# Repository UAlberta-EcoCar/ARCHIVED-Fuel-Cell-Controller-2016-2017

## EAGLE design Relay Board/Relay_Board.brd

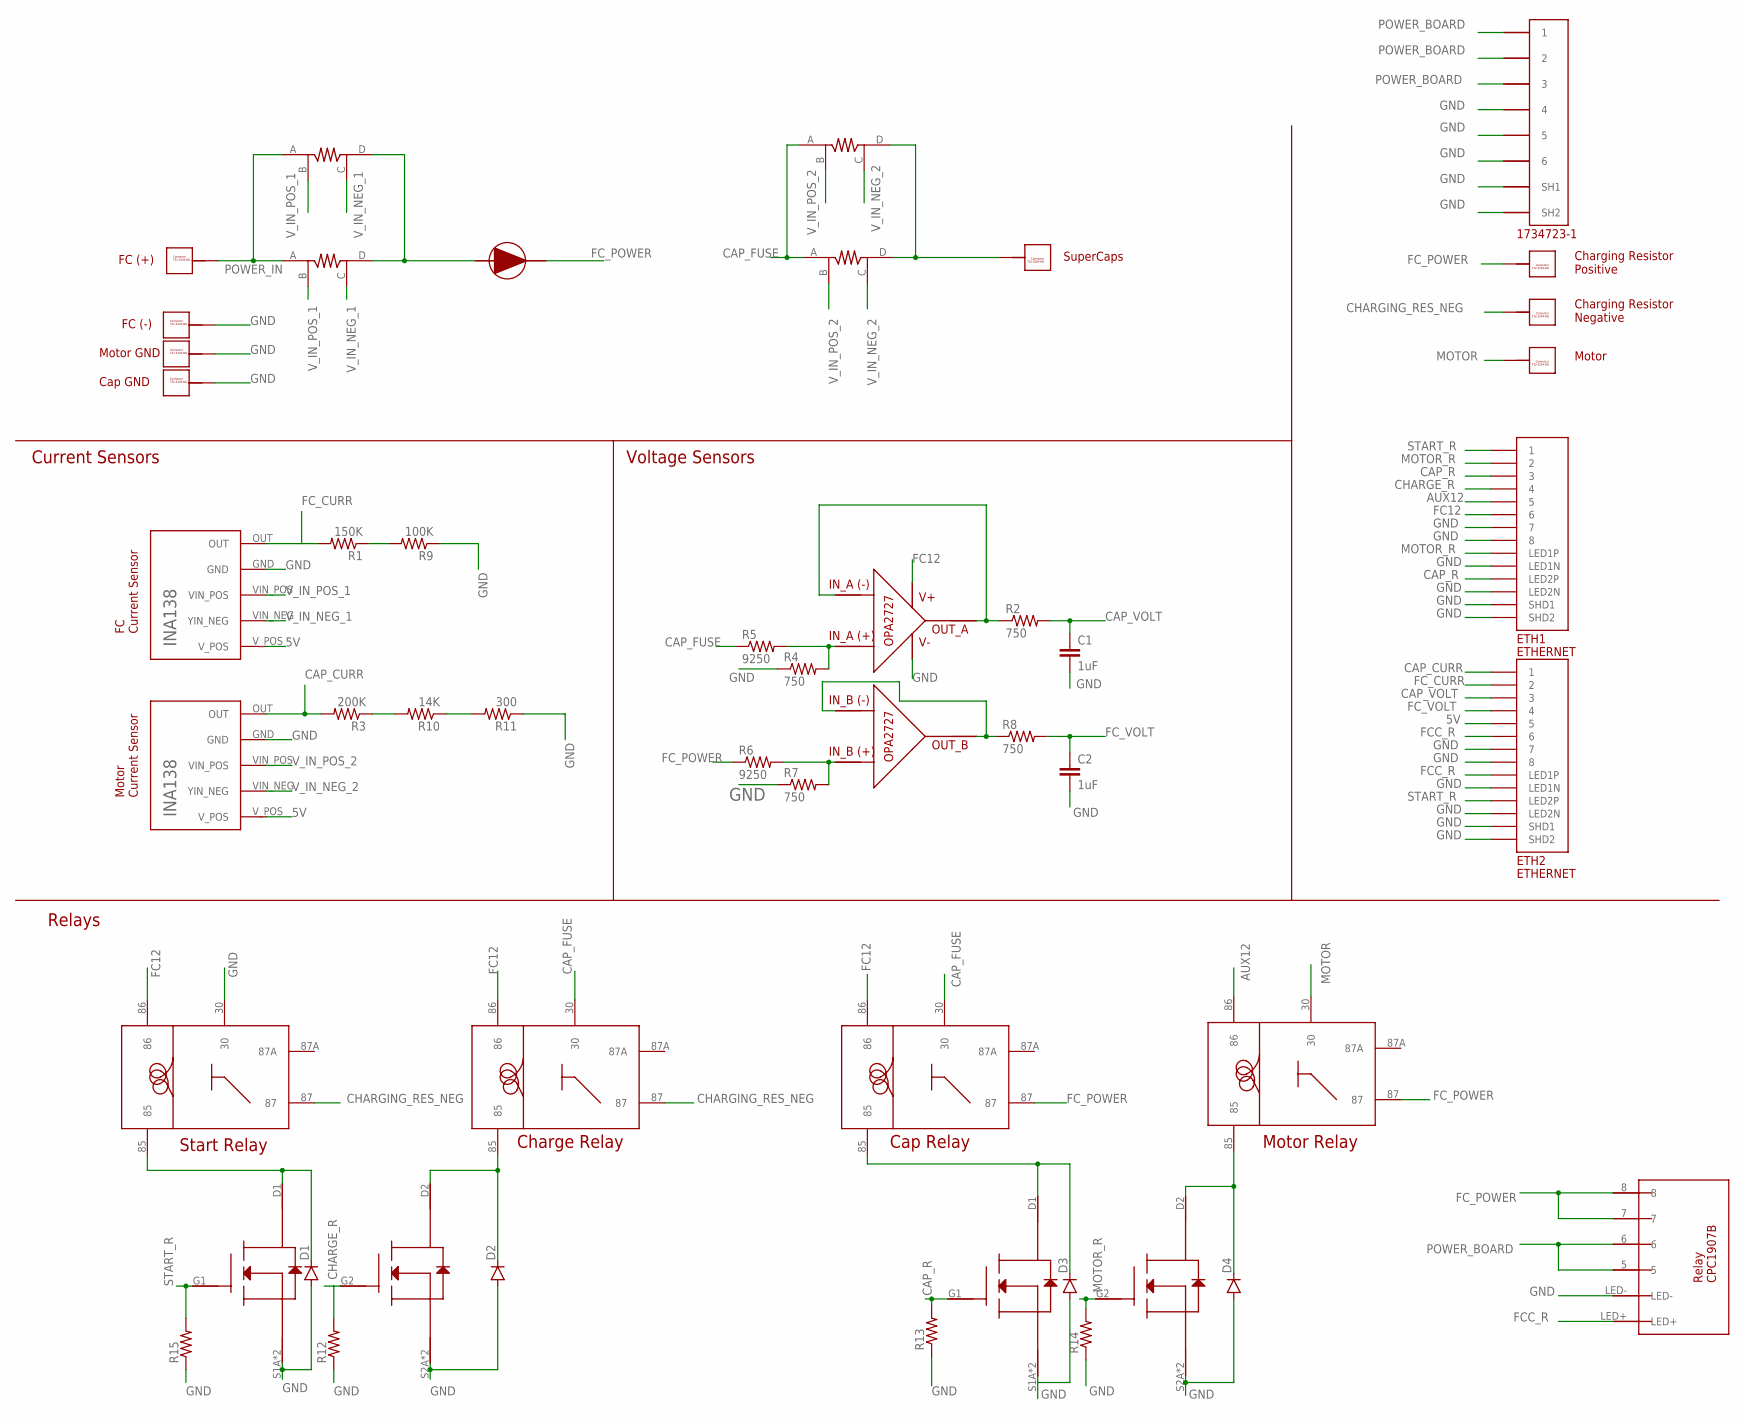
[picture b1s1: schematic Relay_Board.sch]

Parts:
C1, C2: 1uF; 0402-CAP
D1, D2, D3, D4: DIODESOD123; SOD-123
ETH1, ETH2: ETHERNET; A122645-ND
R1: 150K; 1206
R2, R4, R7, R8: 750; 1206
R3: 200K; 1206
R5, R6: 9250; 1206
R9: 100K; 1206
R10: 14K; 1206
R11: 300; 1206
R12, R13, R14, R15: RESISTOR0603-RES; 0603-RES
U$1, U$2, U$10, U$13, U$14, U$20, U$23, U$24: 732-3204-ND_CONNECTOR; 732-3204-ND
U$3, U$7: TI_INA138
U$4, U$6, U$12, U$21: SHUNT_RESISTOR_CSM3637; CSM3637
U$5: DIODE-APT60S20BG
U$8, U$11, U$15, U$18: VCF4-1000
U$9, U$25: SI6926ADQ-T1-E3CT-ND_MOSFET
U$17: OP-AMP_OPA2727AIDR
U$19: 5555140-6; 1734723-1_RJ11
U$22: RELAY-CPC1907B

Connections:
5V: ETH2.P$5 (5), U$3.V_POS, U$7.V_POS
AUX12: ETH1.P$5 (5), U$18.86
CAP_CURR: ETH2.P$1 (1), R3.2, U$3.OUT
CAP_FUSE: R5.1, U$8.30, U$11.30, U$12.A, U$21.A
CAP_R: ETH1.P$3 (3), ETH1.P$12 (LED2P), R13.2, U$9.G1
CAP_VOLT: C1.1, ETH2.P$3 (3), R2.2
CHARGE_R: ETH1.P$4 (4), R12.2, U$25.G2
CHARGING_RES_NEG: U$11.87, U$14.P$1, U$14.P$2, U$14.P$3, U$14.P$4, U$14.P$5, U$14.P$6, U$14.P$7, U$14.P$8, U$14.P$9, U$14.P$10, U$15.87
FC12: ETH1.P$6 (6), U$8.86, U$11.86, U$15.86, U$17.V+
FCC_R: ETH2.P$6 (6), ETH2.P$10 (LED1P), U$22.LED+
FC_CURR: ETH2.P$2 (2), R1.2, U$7.OUT
FC_POWER: R6.1, U$5.CATHODE, U$8.87, U$13.P$1, U$13.P$2, U$13.P$3, U$13.P$4, U$13.P$5, U$13.P$6, U$13.P$7, U$13.P$8, U$13.P$9, U$13.P$10, U$18.87, U$22.7, U$22.8
FC_VOLT: C2.1, ETH2.P$4 (4), R8.2
GND: C1.2, C2.2, D1.A, D2.A, D3.A, D4.A, ETH1.P$7 (7), ETH1.P$8 (8), ETH1.P$9 (LED1N), ETH1.P$11 (LED2N), ETH1.P$13 (SHD1), ETH1.P$14 (SHD2), ETH2.P$7 (7), ETH2.P$8 (8), ETH2.P$9 (LED1N), ETH2.P$11 (LED2N), ETH2.P$13 (SHD1), ETH2.P$14 (SHD2), R4.1, R7.1, R9.1, R11.1, R12.1, R13.1, R14.1, R15.1, U$2.P$1, U$2.P$2, U$2.P$3, U$2.P$4, U$2.P$5, U$2.P$6, U$2.P$7, U$2.P$8, U$2.P$9, U$2.P$10, U$3.GND, U$7.GND, U$9.S1A (S1), U$9.S1B (S1), U$9.S2A (S2), U$9.S2B (S2), U$15.30, U$17.V-, U$19.4, U$19.5, U$19.6, U$19.SH1, U$19.SH2, U$22.LED-, U$23.P$1, U$23.P$2, U$23.P$3, U$23.P$4, U$23.P$5, U$23.P$6, U$23.P$7, U$23.P$8, U$23.P$9, U$23.P$10, U$24.P$1, U$24.P$2, U$24.P$3, U$24.P$4, U$24.P$5, U$24.P$6, U$24.P$7, U$24.P$8, U$24.P$9, U$24.P$10, U$25.S1A (S1), U$25.S1B (S1), U$25.S2A (S2), U$25.S2B (S2)
MOTOR: U$18.30, U$20.P$1, U$20.P$2, U$20.P$3, U$20.P$4, U$20.P$5, U$20.P$6, U$20.P$7, U$20.P$8, U$20.P$9, U$20.P$10
MOTOR_R: ETH1.P$2 (2), ETH1.P$10 (LED1P), R14.2, U$9.G2
unnamed: R1.1, R9.2
unnamed: D3.C, U$8.85, U$9.D1
unnamed: D1.C, U$15.85, U$25.D1
unnamed: D2.C, U$11.85, U$25.D2
unnamed: R4.2, R5.2, U$17.IN_A+
unnamed: R6.2, R7.2, U$17.IN_B+
unnamed: R8.1, U$17.IN_B-, U$17.OUT_B
unnamed: R2.1, U$17.IN_A-, U$17.OUT_A
unnamed: R3.1, R10.2
unnamed: R10.1, R11.2
unnamed: D4.C, U$9.D2, U$18.85
POWER_BOARD: U$19.1, U$19.2, U$19.3, U$22.5, U$22.6
POWER_IN: U$1.P$1, U$1.P$2, U$1.P$3, U$1.P$4, U$1.P$5, U$1.P$6, U$1.P$7, U$1.P$8, U$1.P$9, U$1.P$10, U$4.A, U$6.A
SHUNT_RES_1: U$4.D, U$5.ANODE, U$6.D
START_R: ETH1.P$1 (1), ETH2.P$12 (LED2P), R15.2, U$25.G1
SUPERCAPS: U$10.P$1, U$10.P$2, U$10.P$3, U$10.P$4, U$10.P$5, U$10.P$6, U$10.P$7, U$10.P$8, U$10.P$9, U$10.P$10, U$12.D, U$21.D
V_IN_NEG_1: U$4.C, U$6.C, U$7.VIN_NEG (YIN_NEG)
V_IN_NEG_2: U$3.VIN_NEG (YIN_NEG), U$12.C, U$21.C
V_IN_POS_1: U$4.B, U$6.B, U$7.VIN_POS
V_IN_POS_2: U$3.VIN_POS, U$12.B, U$21.B

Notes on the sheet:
FC Current Sensor
SuperCaps
Charging Resistor Positive
Charging Resistor Negative
Motor Current Sensor
FC (+)
FC (-)
Motor
Voltage Sensors
Current Sensors
Relays
Cap Relay
Charge Relay
Start Relay
Motor Relay
Motor GND
Cap GND

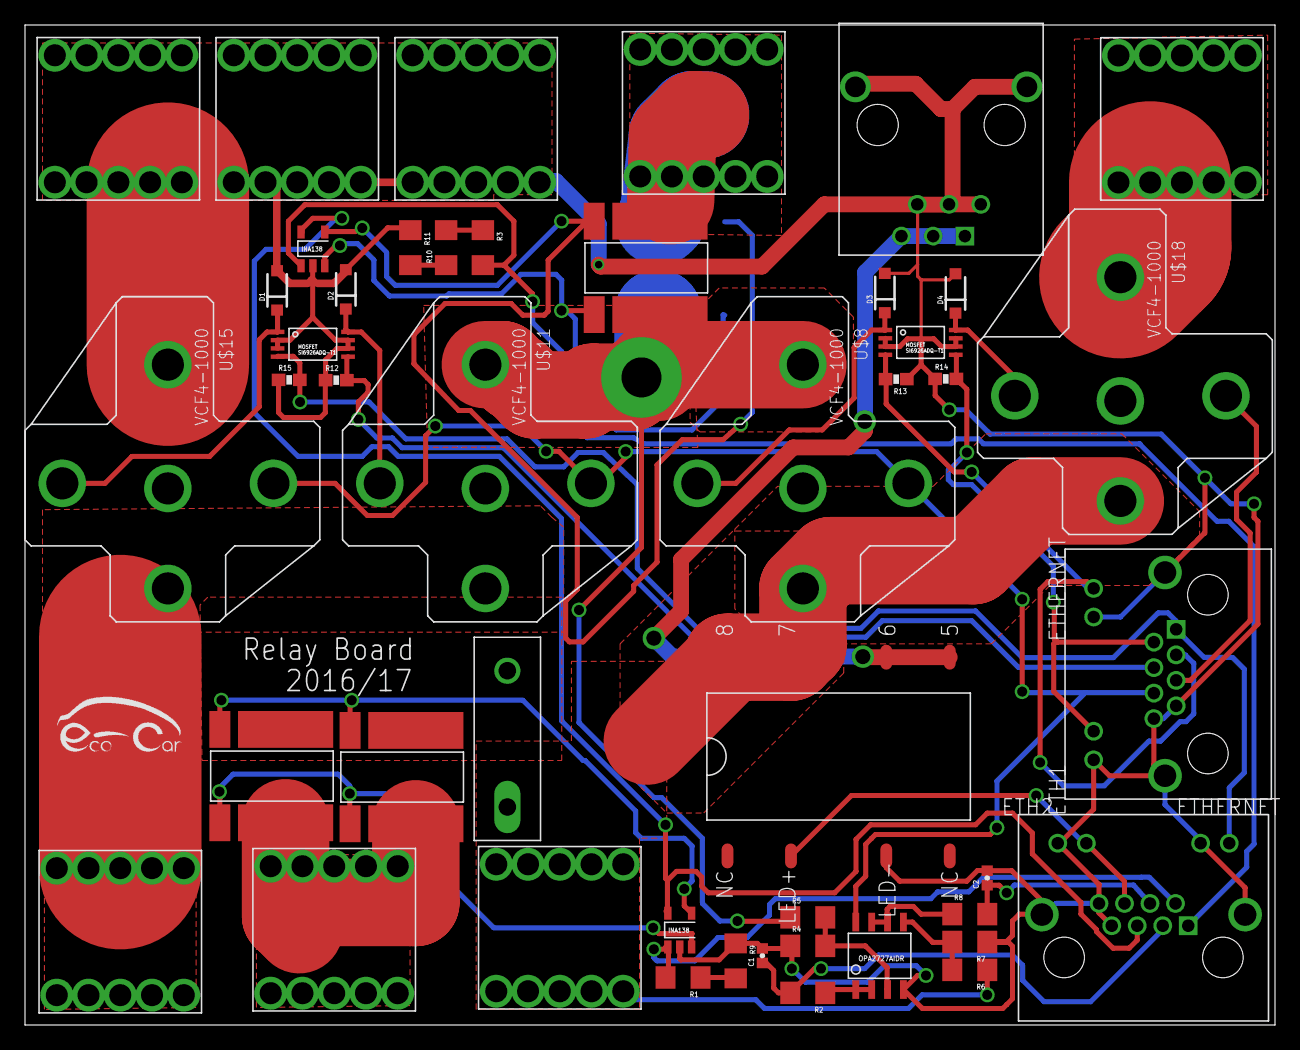
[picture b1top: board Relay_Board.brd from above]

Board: 2 copper layers, 100.0 x 80.0 mm, 48 parts (1 on the bottom side), 36 nets.

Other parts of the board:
U$16: LOGO

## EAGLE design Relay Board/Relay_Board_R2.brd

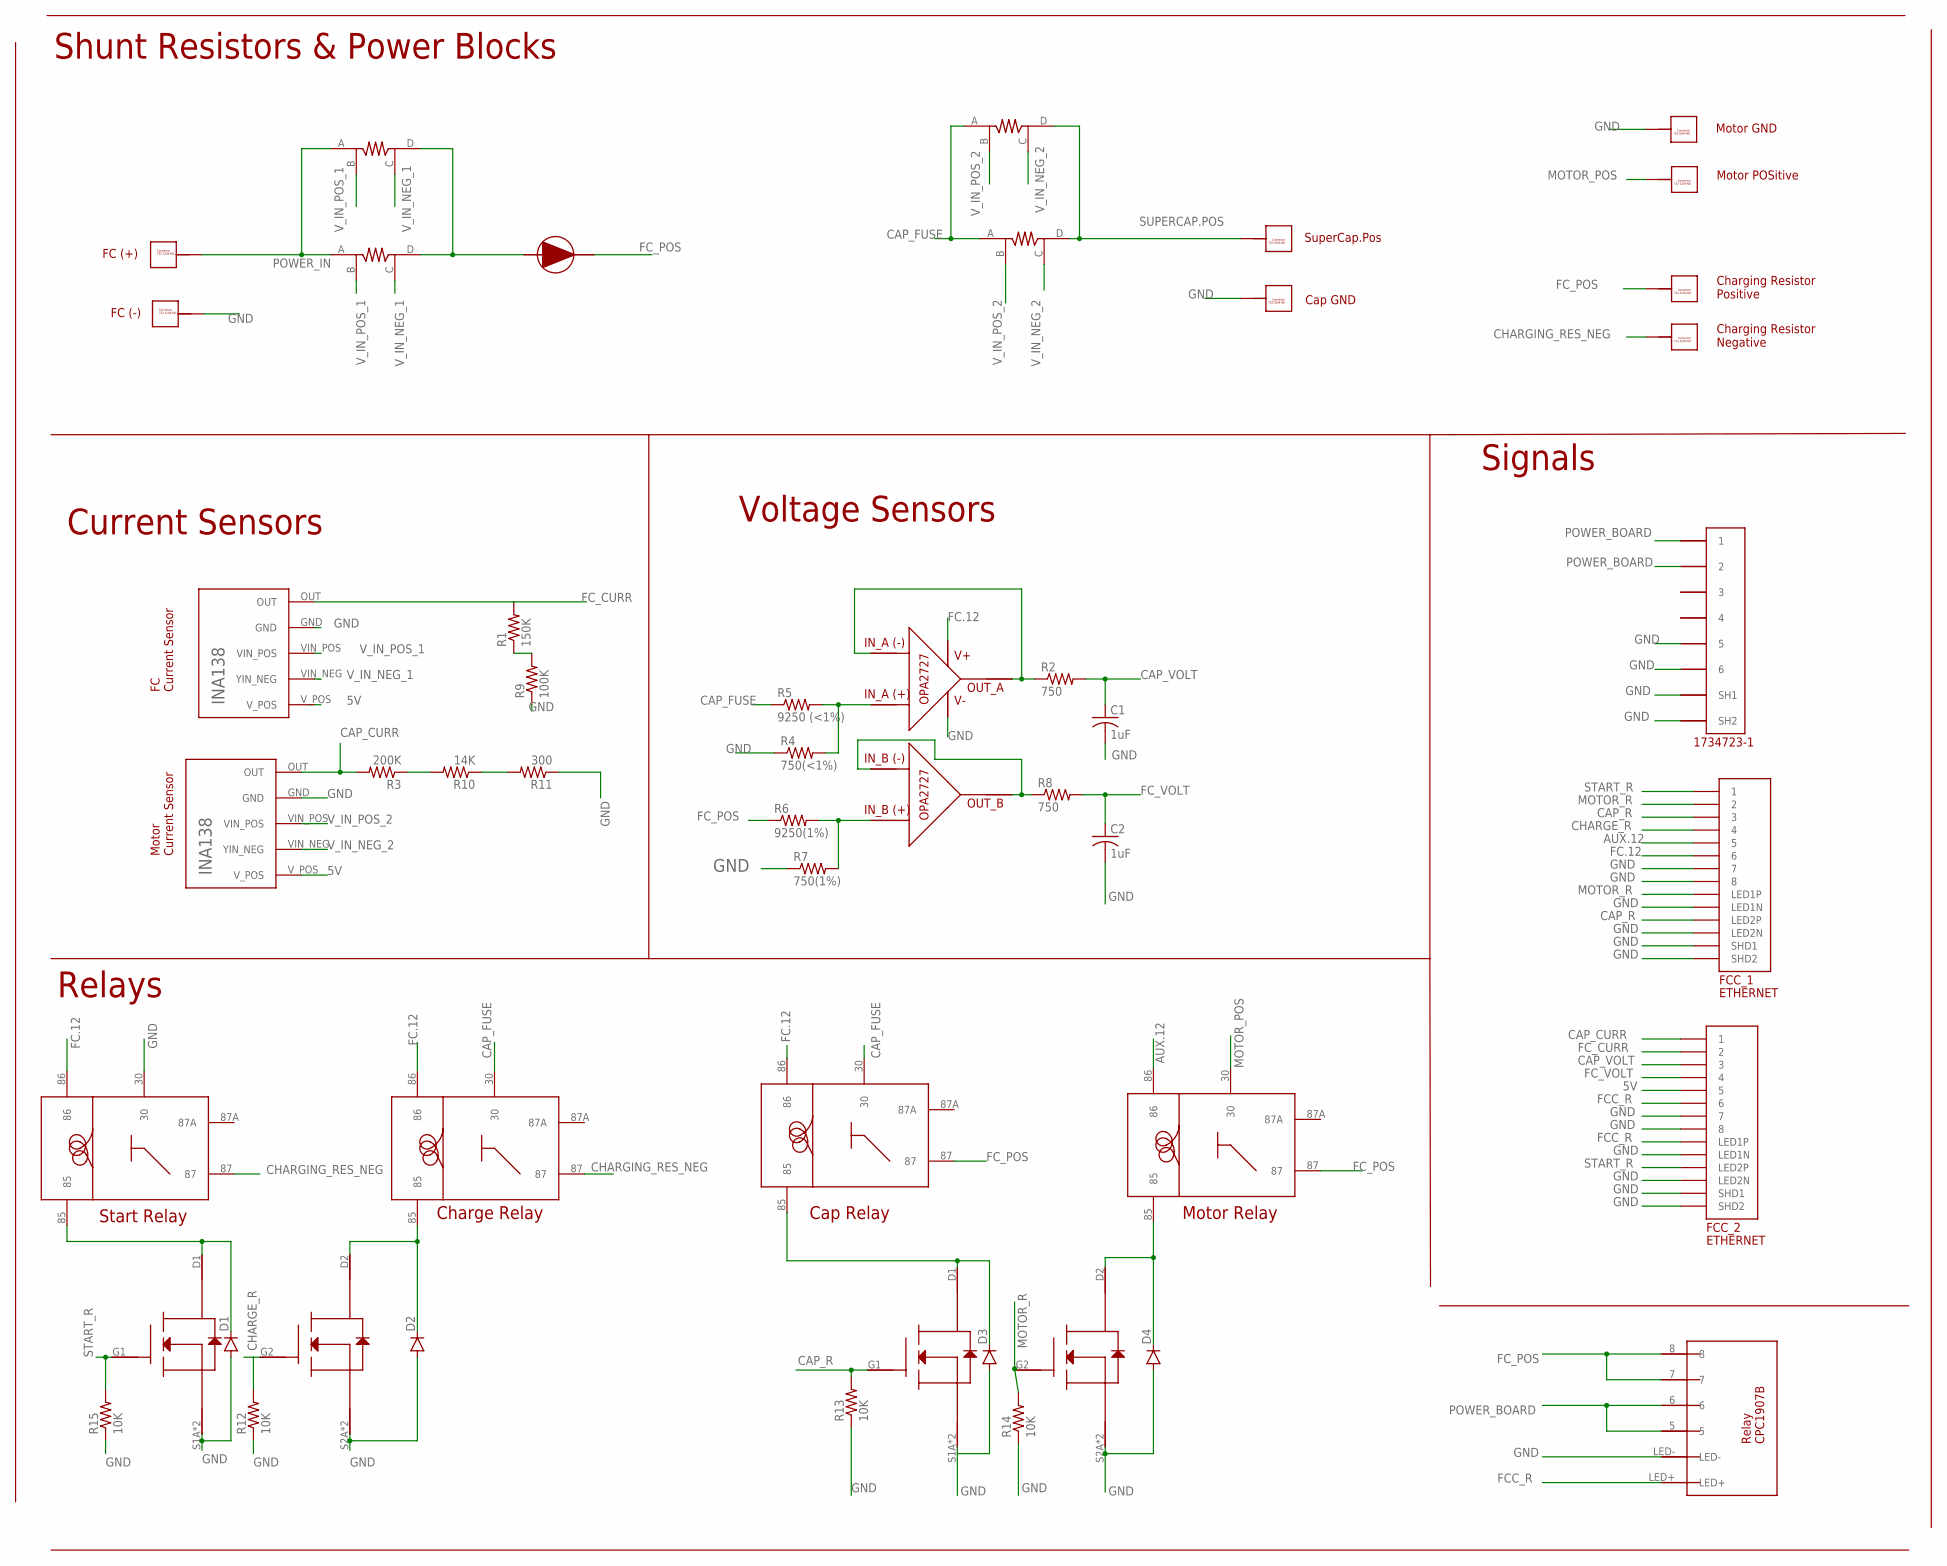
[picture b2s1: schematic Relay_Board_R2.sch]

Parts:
C1, C2: 1uF; C0805
CAP.GND, CAP.POS: 732-3204-ND_CONNECTOR; 732-3204-ND
CAP.RELAY: VCF4-1000
CAP.SHUNT.1, CAP.SHUNT.2: SHUNT_RESISTOR_CSM3637; CSM3637
CHARGE_RELAY: VCF4-1000
D1, D2, D3, D4: DIODESOD123; SOD-123
FC.CURR.SENSOR: TI_INA138
FC.GND, FC.POS: 732-3204-ND_CONNECTOR; 732-3204-ND
FC.SHUNT.1, FC.SHUNT.2: SHUNT_RESISTOR_CSM3637; CSM3637
FCC_1, FCC_2: ETHERNET; A122645-ND
FC_DIODE: DIODE-APT60S20BG
MOTOR.CURR.SENSOR: TI_INA138
MOTOR.GROUND, MOTOR.POSITIVE: 732-3204-ND_CONNECTOR; 732-3204-ND
MOTOR.RELAY: VCF4-1000
R1: 150K; R0805
R2, R8: 750; R0805
R3: 200K; R0805
R4: 750(<1%); R0805
R5: 9250 (<1%); R0805
R6: 9250(1%); R0805
R7: 750(1%); R0805
R9: 100K; R0805
R10: 14K; R0805
R11: 300; R0805
R12, R13, R14, R15: 10K; R0805
RES.NEG, RES.POS: 732-3204-ND_CONNECTOR; 732-3204-ND
START.RELAY: VCF4-1000
U$9, U$25: SI6926ADQ-T1-E3CT-ND_MOSFET
U$17: OP-AMP_OPA2727AIDR
U$19: 5555140-6; 1734723-1_RJ11
U$22: RELAY-CPC1907B

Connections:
5V: FC.CURR.SENSOR.V_POS, FCC_2.P$5 (5), MOTOR.CURR.SENSOR.V_POS
AUX.12: FCC_1.P$5 (5), MOTOR.RELAY.86
CAP_CURR: FCC_2.P$1 (1), MOTOR.CURR.SENSOR.OUT, R3.2
CAP_FUSE: CAP.RELAY.30, CAP.SHUNT.1.A, CAP.SHUNT.2.A, CHARGE_RELAY.30, R5.1
CAP_R: FCC_1.P$3 (3), FCC_1.P$12 (LED2P), R13.2, U$9.G1
CAP_VOLT: C1.1, FCC_2.P$3 (3), R2.2
CHARGE_R: FCC_1.P$4 (4), R12.2, U$25.G2
CHARGING_RES_NEG: CHARGE_RELAY.87, RES.NEG.P$1, RES.NEG.P$2, RES.NEG.P$3, RES.NEG.P$4, RES.NEG.P$5, RES.NEG.P$6, RES.NEG.P$7, RES.NEG.P$8, RES.NEG.P$9, RES.NEG.P$10, START.RELAY.87
FC.12: CAP.RELAY.86, CHARGE_RELAY.86, FCC_1.P$6 (6), START.RELAY.86, U$17.V+
FCC_R: FCC_2.P$6 (6), FCC_2.P$10 (LED1P), U$22.LED+
FC_CURR: FC.CURR.SENSOR.OUT, FCC_2.P$2 (2), R1.2
FC_POS: CAP.RELAY.87, FC_DIODE.CATHODE, MOTOR.RELAY.87, R6.1, RES.POS.P$1, RES.POS.P$2, RES.POS.P$3, RES.POS.P$4, RES.POS.P$5, RES.POS.P$6, RES.POS.P$7, RES.POS.P$8, RES.POS.P$9, RES.POS.P$10, U$22.7, U$22.8
FC_VOLT: C2.1, FCC_2.P$4 (4), R8.2
GND: C1.2, C2.2, CAP.GND.P$1, CAP.GND.P$2, CAP.GND.P$3, CAP.GND.P$4, CAP.GND.P$5, CAP.GND.P$6, CAP.GND.P$7, CAP.GND.P$8, CAP.GND.P$9, CAP.GND.P$10, D1.A, D2.A, D3.A, D4.A, FC.CURR.SENSOR.GND, FC.GND.P$1, FC.GND.P$2, FC.GND.P$3, FC.GND.P$4, FC.GND.P$5, FC.GND.P$6, FC.GND.P$7, FC.GND.P$8, FC.GND.P$9, FC.GND.P$10, FCC_1.P$7 (7), FCC_1.P$8 (8), FCC_1.P$9 (LED1N), FCC_1.P$11 (LED2N), FCC_1.P$13 (SHD1), FCC_1.P$14 (SHD2), FCC_2.P$7 (7), FCC_2.P$8 (8), FCC_2.P$9 (LED1N), FCC_2.P$11 (LED2N), FCC_2.P$13 (SHD1), FCC_2.P$14 (SHD2), MOTOR.CURR.SENSOR.GND, MOTOR.GROUND.P$1, MOTOR.GROUND.P$2, MOTOR.GROUND.P$3, MOTOR.GROUND.P$4, MOTOR.GROUND.P$5, MOTOR.GROUND.P$6, MOTOR.GROUND.P$7, MOTOR.GROUND.P$8, MOTOR.GROUND.P$9, MOTOR.GROUND.P$10, R4.1, R7.1, R9.1, R11.1, R12.1, R13.1, R14.1, R15.1, START.RELAY.30, U$9.S1A (S1), U$9.S1B (S1), U$9.S2A (S2), U$9.S2B (S2), U$17.V-, U$19.5, U$19.6, U$19.SH1, U$19.SH2, U$22.LED-, U$25.S1A (S1), U$25.S1B (S1), U$25.S2A (S2), U$25.S2B (S2)
MOTOR_POS: MOTOR.POSITIVE.P$1, MOTOR.POSITIVE.P$2, MOTOR.POSITIVE.P$3, MOTOR.POSITIVE.P$4, MOTOR.POSITIVE.P$5, MOTOR.POSITIVE.P$6, MOTOR.POSITIVE.P$7, MOTOR.POSITIVE.P$8, MOTOR.POSITIVE.P$9, MOTOR.POSITIVE.P$10, MOTOR.RELAY.30
MOTOR_R: FCC_1.P$2 (2), FCC_1.P$10 (LED1P), R14.2, U$9.G2
unnamed: R1.1, R9.2
unnamed: CAP.RELAY.85, D3.C, U$9.D1
unnamed: D1.C, START.RELAY.85, U$25.D1
unnamed: CHARGE_RELAY.85, D2.C, U$25.D2
unnamed: R4.2, R5.2, U$17.IN_A+
unnamed: R6.2, R7.2, U$17.IN_B+
unnamed: R8.1, U$17.IN_B-, U$17.OUT_B
unnamed: R2.1, U$17.IN_A-, U$17.OUT_A
unnamed: R3.1, R10.2
unnamed: R10.1, R11.2
unnamed: D4.C, MOTOR.RELAY.85, U$9.D2
POWER_BOARD: U$19.1, U$19.2, U$22.5, U$22.6
POWER_IN: FC.POS.P$1, FC.POS.P$2, FC.POS.P$3, FC.POS.P$4, FC.POS.P$5, FC.POS.P$6, FC.POS.P$7, FC.POS.P$8, FC.POS.P$9, FC.POS.P$10, FC.SHUNT.1.A, FC.SHUNT.2.A
SHUNT_RES_1: FC.SHUNT.1.D, FC.SHUNT.2.D, FC_DIODE.ANODE
START_R: FCC_1.P$1 (1), FCC_2.P$12 (LED2P), R15.2, U$25.G1
SUPERCAP.POS: CAP.POS.P$1, CAP.POS.P$2, CAP.POS.P$3, CAP.POS.P$4, CAP.POS.P$5, CAP.POS.P$6, CAP.POS.P$7, CAP.POS.P$8, CAP.POS.P$9, CAP.POS.P$10, CAP.SHUNT.1.D, CAP.SHUNT.2.D
V_IN_NEG_1: FC.CURR.SENSOR.VIN_NEG (YIN_NEG), FC.SHUNT.1.C, FC.SHUNT.2.C
V_IN_NEG_2: CAP.SHUNT.1.C, CAP.SHUNT.2.C, MOTOR.CURR.SENSOR.VIN_NEG (YIN_NEG)
V_IN_POS_1: FC.CURR.SENSOR.VIN_POS, FC.SHUNT.1.B, FC.SHUNT.2.B
V_IN_POS_2: CAP.SHUNT.1.B, CAP.SHUNT.2.B, MOTOR.CURR.SENSOR.VIN_POS

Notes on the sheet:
FC Current Sensor
SuperCap.Pos
Charging Resistor Positive
Charging Resistor Negative
Motor Current Sensor
FC (+)
FC (-)
Motor POSitive
Voltage Sensors
Current Sensors
Relays
Cap Relay
Charge Relay
Start Relay
Motor Relay
Motor GND
Cap GND
Shunt Resistors & Power Blocks
Signals

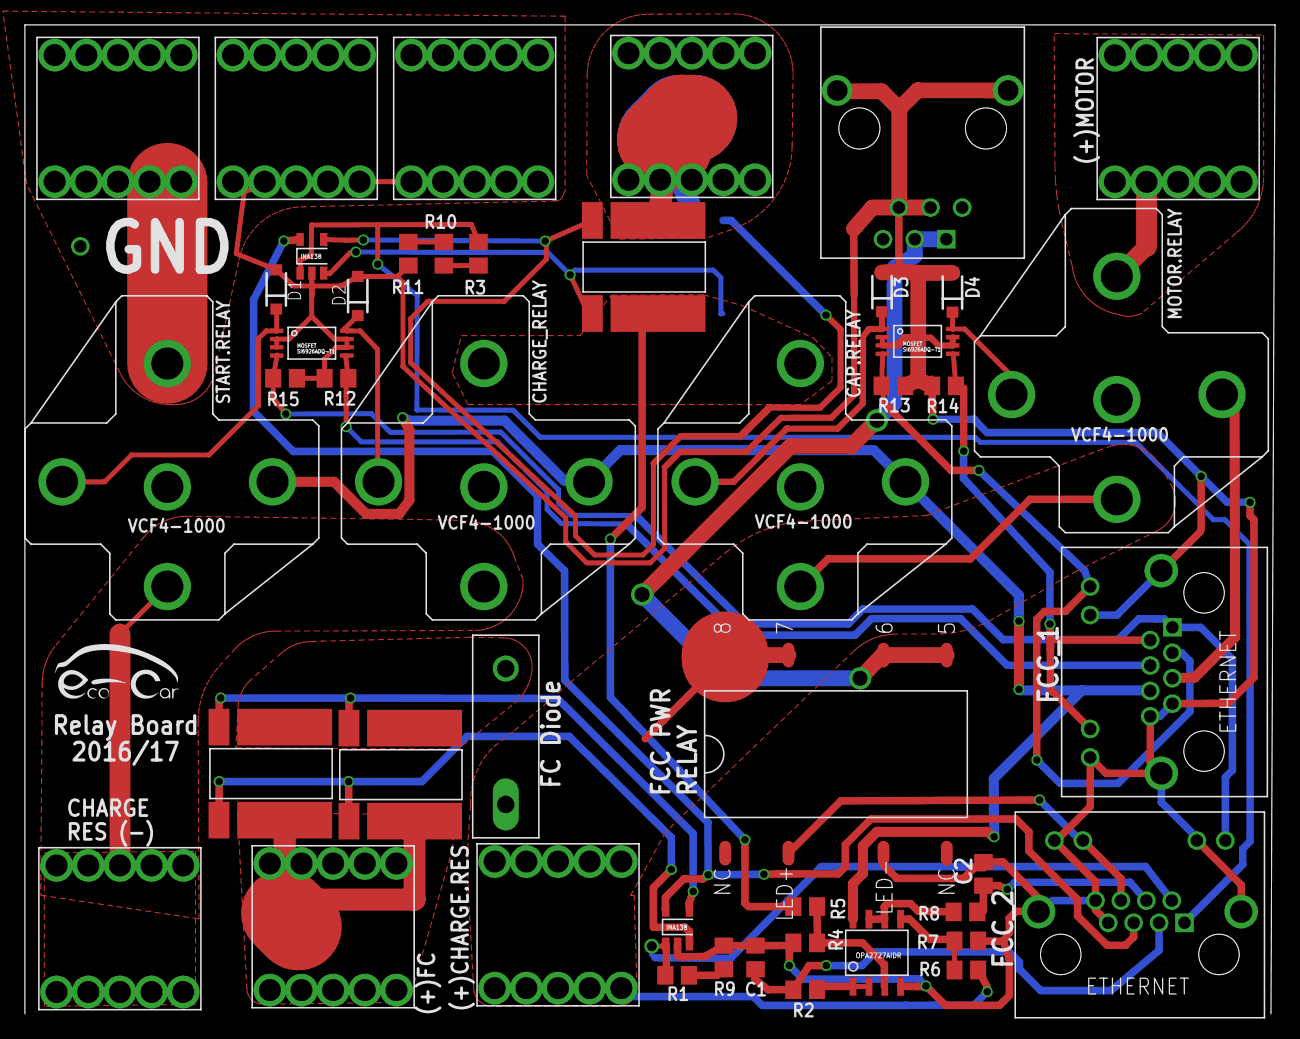
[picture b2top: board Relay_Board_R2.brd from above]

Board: 2 copper layers, 100.3 x 79.4 mm, 48 parts (1 on the bottom side), 36 nets.

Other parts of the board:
U$16: LOGO

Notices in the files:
parts and their libraries:
SparkFun-Capacitors: Licensing: Creative Commons ShareAlike 4.0 International - https://creativecommons.org/licenses/by-sa/4.0
